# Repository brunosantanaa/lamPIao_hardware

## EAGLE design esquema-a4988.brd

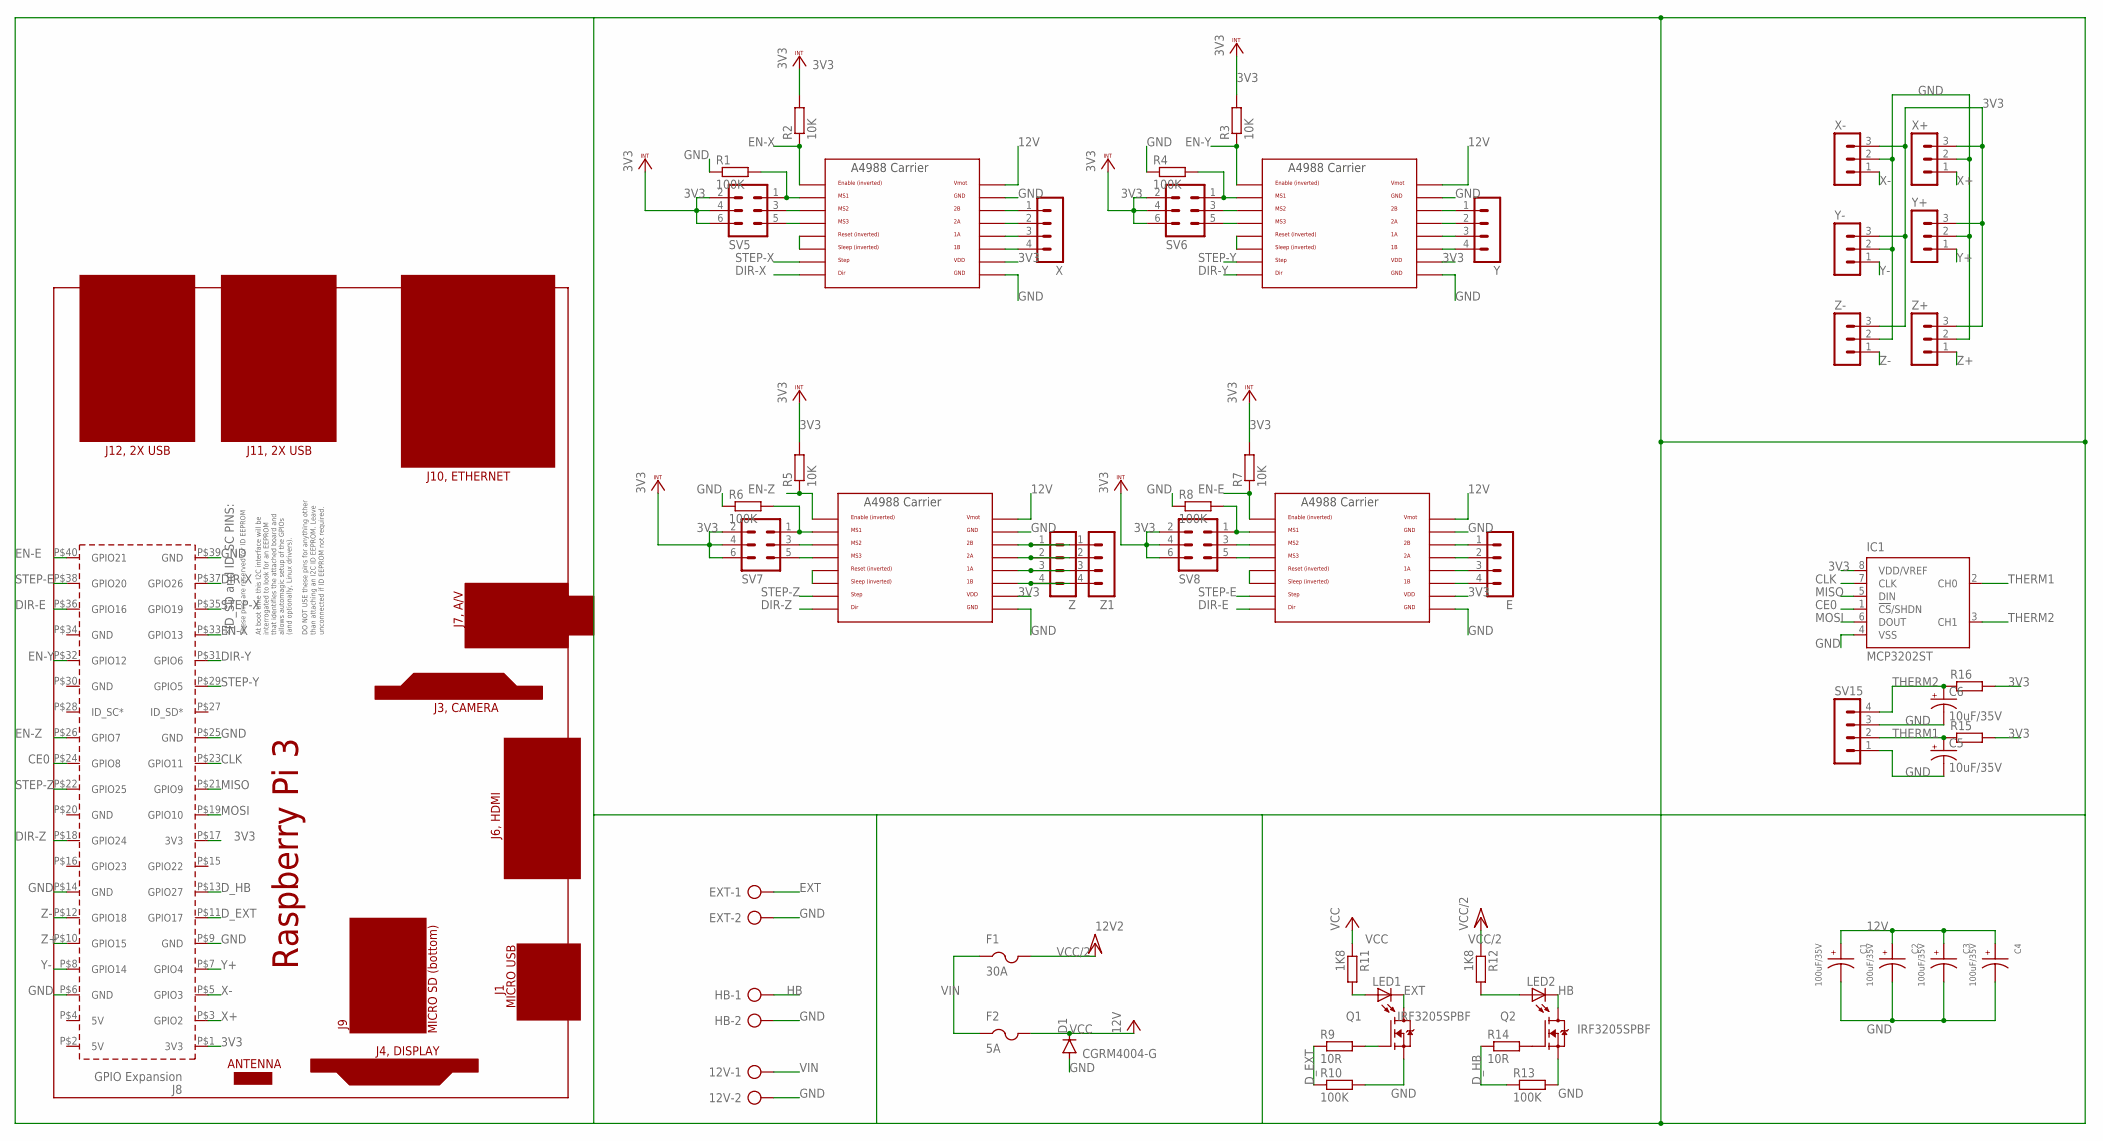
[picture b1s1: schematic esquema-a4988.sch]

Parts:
12V: AK500/2
C1, C2, C3, C4: 100uF/35V; CAPAE660X800N
C5, C6: 10uF/35V; 153CLV-0405
D1: CGRM4004-G; SOD-123_MINI-SMA
E: MA04-1
EXT: AK500/2
F1: 30A; R1206
F2: 5A; R1206
HB: AK500/2
IC1: MCP3202ST; TSSOP8
LED1, LED2: LEDCHIPLED_1206; CHIPLED_1206
PCB1: RPI3RPI3; RPI3
Q1, Q2: IRF3205SPBF; TRANS_IRF3205SPBF
R1, R4, R6, R8, R10, R13: 100K; R1206
R2, R3, R5, R7: 10K; R1206
R9, R14: 10R; R1206
R11, R12: 1K8; R1206
R15, R16: RR1206; R1206
SV5, SV6, SV7, SV8: MA03-2
SV15: MA04-1
U$1, U$2, U$3, U$4: A4983CARRIER; A4988BREAKOUT
X: MA04-1
X+: MA03-1
X-: MA03-1
Y: MA04-1
Y+: MA03-1
Y-: MA03-1
Z, Z1: MA04-1
Z+: MA03-1
Z-: MA03-1

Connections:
3V3: IC1.8 (VDD/VREF), PCB1.P$1 (3V3), PCB1.P$17 (3V3), R2.2, R3.2, R5.2, R7.2, R15.2, R16.2, SV5.2, SV5.4, SV5.6, SV6.2, SV6.4, SV6.6, SV7.2, SV7.4, SV7.6, SV8.2, SV8.4, SV8.6, U$1.VDD, U$2.VDD, U$3.VDD, U$4.VDD, X+.3, X-.3, Y+.3, Y-.3, Z+.3, Z-.3
12V: C1.1, C2.1, C3.1, C4.1, U$1.VMOT, U$2.VMOT, U$3.VMOT, U$4.VMOT
CE0: IC1.1 (!CS!/SHDN), PCB1.P$24 (GPIO8)
CLK: IC1.7 (CLK), PCB1.P$23 (GPIO11)
DIR-E: PCB1.P$36 (GPIO16), U$4.DIR
DIR-X: PCB1.P$37 (GPIO26), U$1.DIR
DIR-Y: PCB1.P$31 (GPIO6), U$2.DIR
DIR-Z: PCB1.P$18 (GPIO24), U$3.DIR
D_EXT: PCB1.P$11 (GPIO17), R9.1, R10.1
D_HB: PCB1.P$13 (GPIO27), R13.1, R14.1
EN-E: PCB1.P$40 (GPIO21), R7.1, U$4.EN
EN-X: PCB1.P$33 (GPIO13), R2.1, U$1.EN
EN-Y: PCB1.P$32 (GPIO12), R3.1, U$2.EN
EN-Z: PCB1.P$26 (GPIO7), R5.1, U$3.EN
EXT: EXT.1, LED1.C, Q1.2 (D)
GND: 12V.2, C1.2, C2.2, C3.2, C4.2, C5.-, C6.-, D1.A, EXT.2, HB.2, IC1.4 (VSS), PCB1.P$6 (GND), PCB1.P$9 (GND), PCB1.P$14 (GND), PCB1.P$25 (GND), PCB1.P$39 (GND), Q1.3 (S), Q2.3 (S), R1.1, R4.1, R6.1, R8.1, R10.2, R13.2, SV15.1, SV15.3, U$1.GND, U$1.GND@0 (GND), U$2.GND, U$2.GND@0 (GND), U$3.GND, U$3.GND@0 (GND), U$4.GND, U$4.GND@0 (GND), X+.2, X-.2, Y+.2, Y-.2, Z+.2, Z-.2
HB: HB.1, LED2.C, Q2.2 (D)
MISO: IC1.5 (DIN), PCB1.P$21 (GPIO9)
MOSI: IC1.6 (DOUT), PCB1.P$19 (GPIO10)
unnamed: R1.2, SV5.1, U$1.MS1
unnamed: SV5.3, U$1.MS2
unnamed: SV5.5, U$1.MS3
unnamed: R4.2, SV6.1, U$2.MS1
unnamed: SV6.3, U$2.MS2
unnamed: SV6.5, U$2.MS3
unnamed: R6.2, SV7.1, U$3.MS1
unnamed: SV7.3, U$3.MS2
unnamed: SV7.5, U$3.MS3
unnamed: R8.2, SV8.1, U$4.MS1
unnamed: SV8.3, U$4.MS2
unnamed: SV8.5, U$4.MS3
unnamed: U$3.2B, Z.1, Z1.1
unnamed: U$3.2A, Z.2, Z1.2
unnamed: U$3.1A, Z.3, Z1.3
unnamed: U$3.1B, Z.4, Z1.4
unnamed: E.1, U$4.2B
unnamed: E.2, U$4.2A
unnamed: E.3, U$4.1A
unnamed: E.4, U$4.1B
unnamed: U$2.2B, Y.1
unnamed: U$2.2A, Y.2
unnamed: U$2.1A, Y.3
unnamed: U$2.1B, Y.4
unnamed: U$1.2B, X.1
unnamed: U$1.2A, X.2
unnamed: U$1.1A, X.3
unnamed: U$1.1B, X.4
unnamed: LED1.A, R11.2
unnamed: LED2.A, R12.2
unnamed: Q1.1 (G), R9.2
unnamed: Q2.1 (G), R14.2
unnamed: U$3.RST, U$3.SLP (SLEEP)
unnamed: U$4.RST, U$4.SLP (SLEEP)
unnamed: U$2.RST, U$2.SLP (SLEEP)
unnamed: U$1.RST, U$1.SLP (SLEEP)
STEP-E: PCB1.P$38 (GPIO20), U$4.STEP
STEP-X: PCB1.P$35 (GPIO19), U$1.STEP
STEP-Y: PCB1.P$29 (GPIO5), U$2.STEP
STEP-Z: PCB1.P$22 (GPIO25), U$3.STEP
THERM1: C5.+, IC1.2 (CH0), R15.1, SV15.2
THERM2: C6.+, IC1.3 (CH1), R16.1, SV15.4
VCC: D1.C, F2.2, R11.1
VCC/2: F1.2, R12.1
VIN: 12V.1, F1.1, F2.1
X+: PCB1.P$3 (GPIO2), X+.1
X-: PCB1.P$5 (GPIO3), X-.1
Y+: PCB1.P$7 (GPIO4), Y+.1
Y-: PCB1.P$8 (GPIO14), Y-.1
Z+: PCB1.P$10 (GPIO15), Z+.1
Z-: PCB1.P$12 (GPIO18), Z-.1

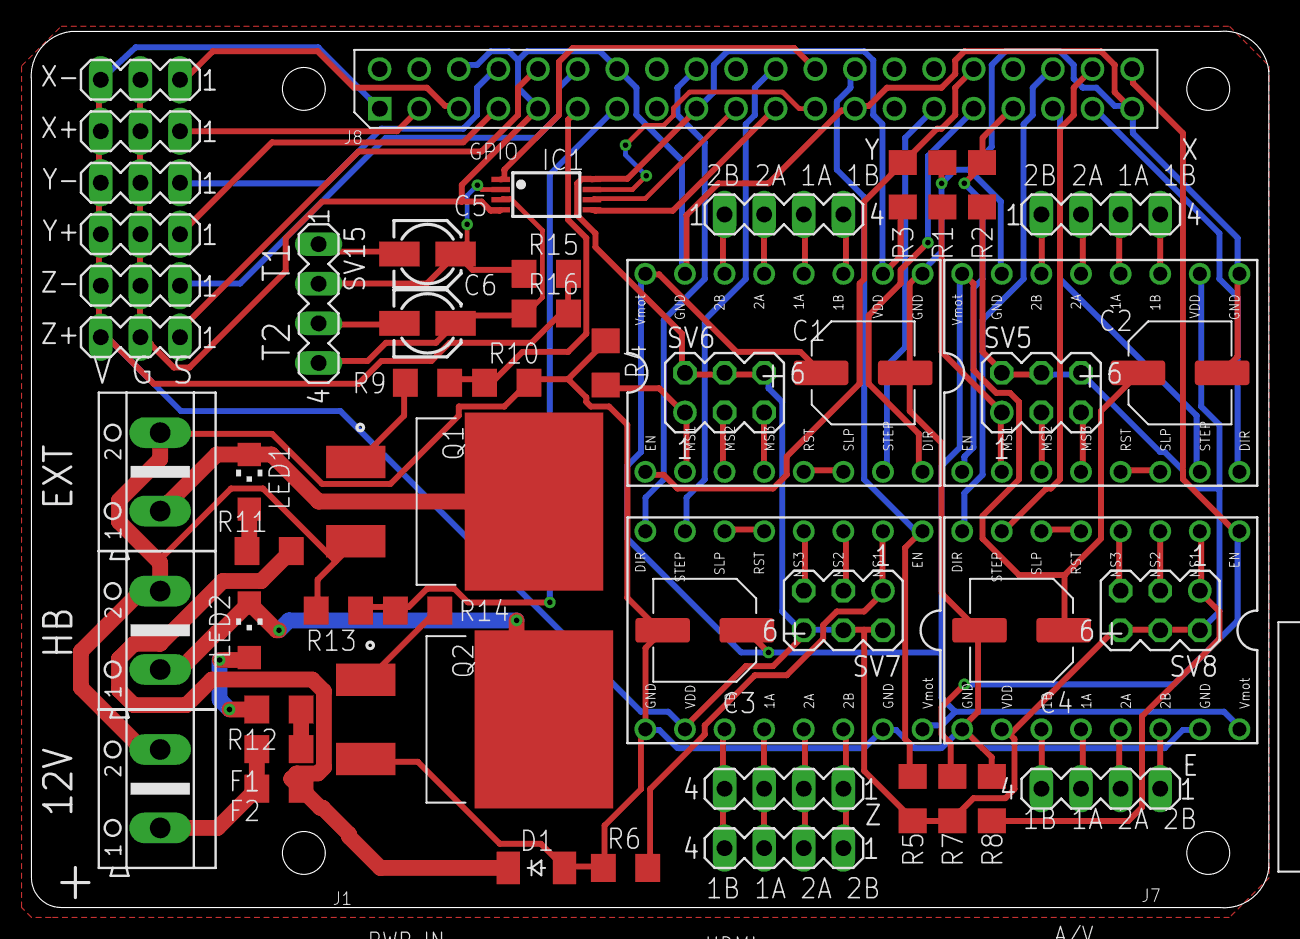
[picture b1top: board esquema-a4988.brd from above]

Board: 2 copper layers, 79.4 x 56.2 mm, 54 parts (0 on the bottom side), 70 nets.
